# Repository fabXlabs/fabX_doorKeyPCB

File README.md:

# fabX_doorKeyPCB

## Not yet functional

Outdoor Keypad and reader PCB

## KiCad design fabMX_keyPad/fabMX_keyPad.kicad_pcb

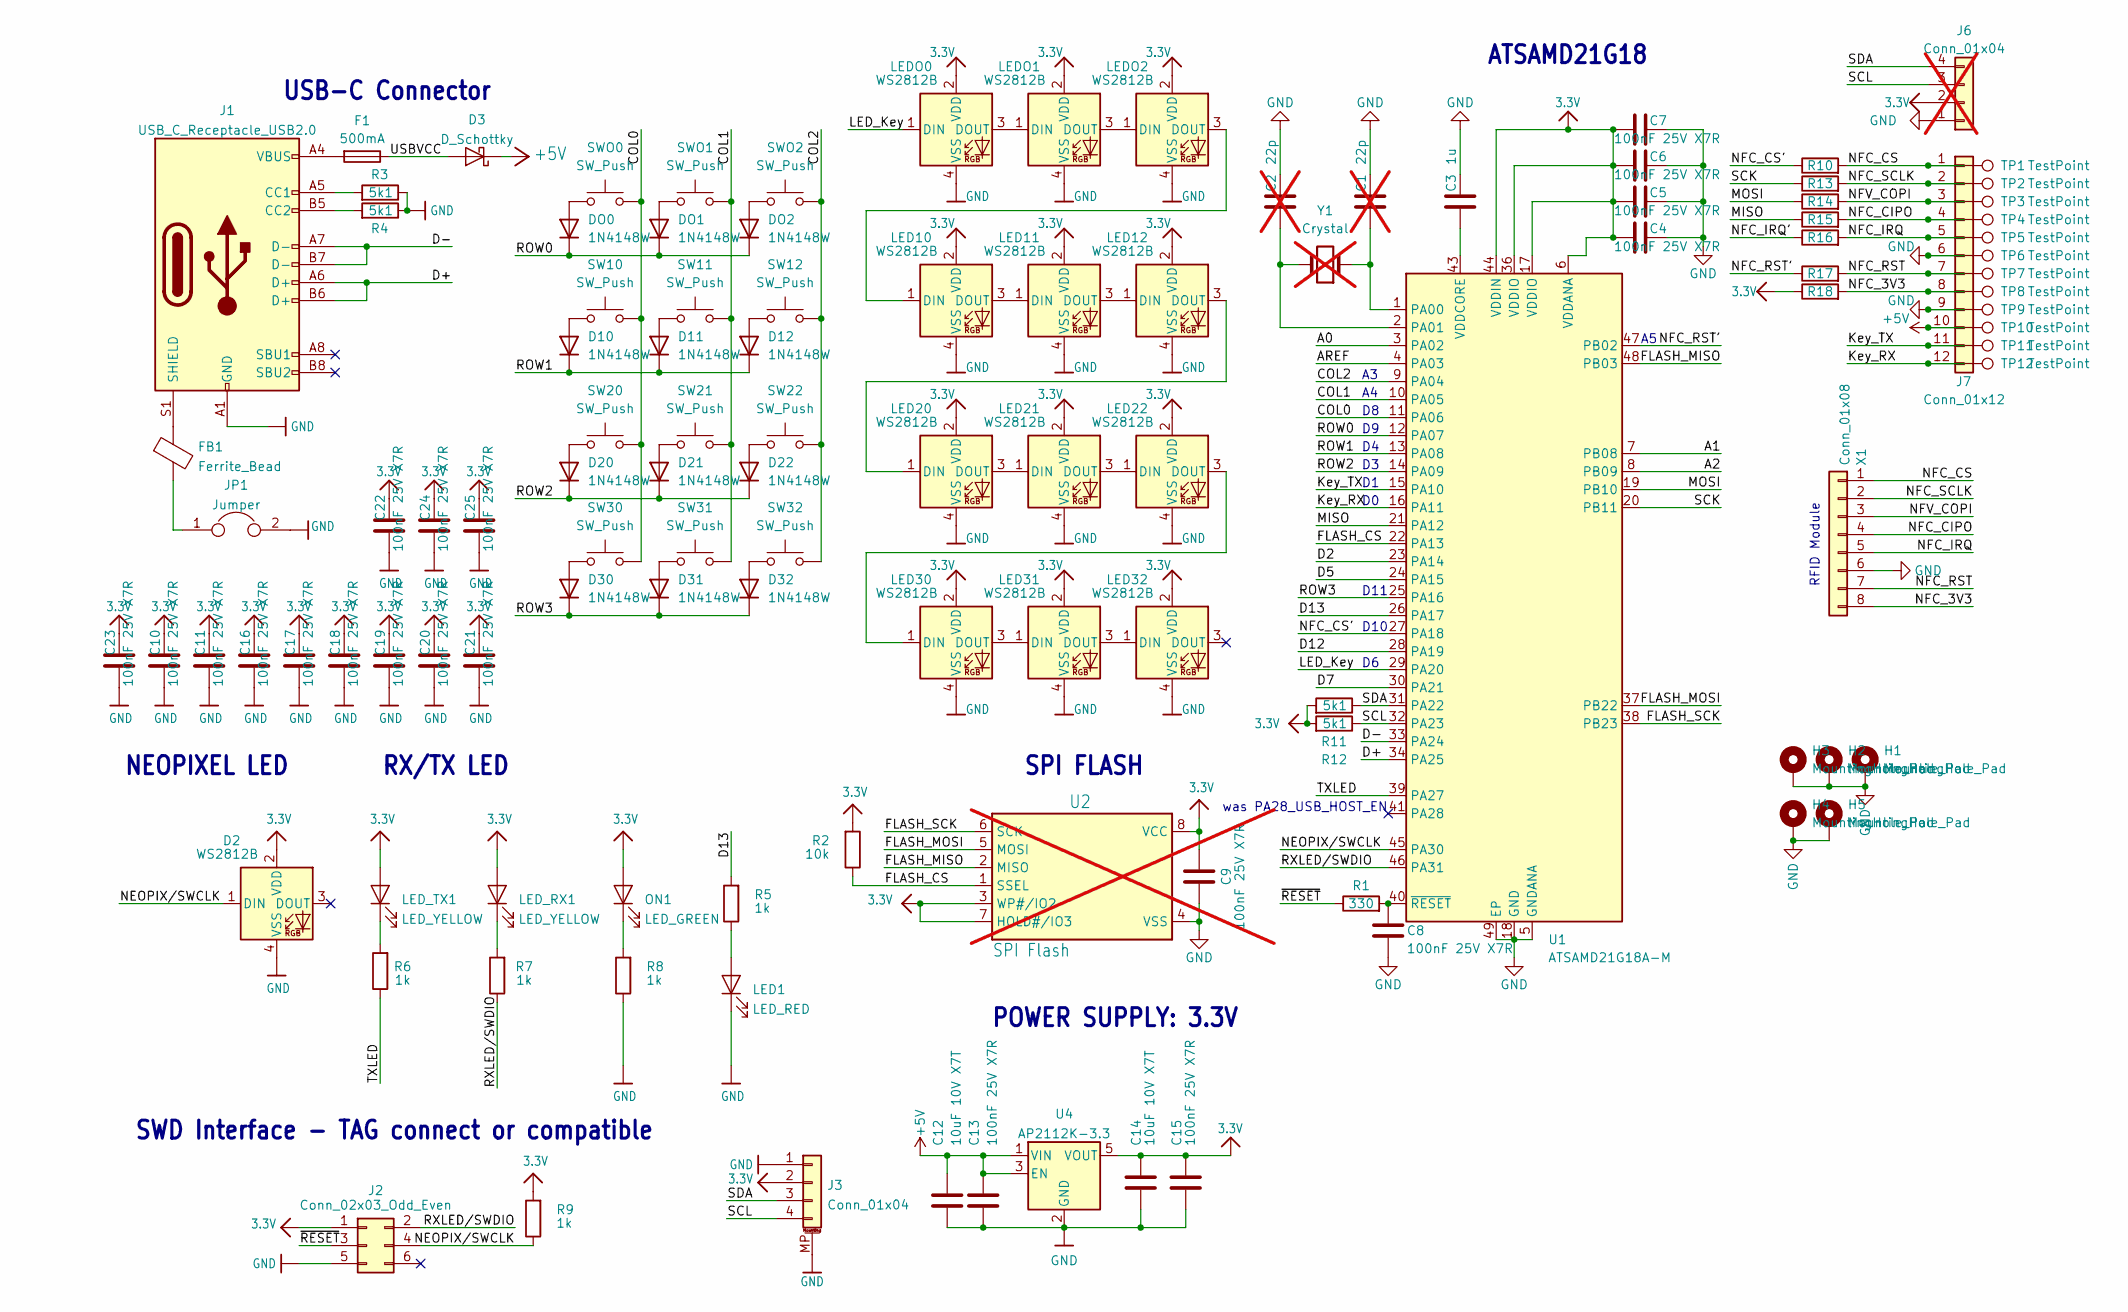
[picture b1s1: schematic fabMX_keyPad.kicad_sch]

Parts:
C1, C2: 22p; C_0603_min; not fitted
C3: 1u; C_0603_min
C4, C5, C6, C7, C8, C9, C10, C11, C13, C15, C16, C17, C18, C19, C20, C21, C22, C23, C24, C25: 100nF 25V X7R; C_0603_min
C12, C14: 10uF 10V X7T; C_0603_min
D2: WS2812B; LED_SK6812_EC15_1.5x1.5mm_modRounded; Digikey# 1528-4492-ND
D3: D_Schottky; D_SOD-123F; Digikey# 4878-SL1MCT-ND
D10, D11, D12, D20, D21, D22, D30, D31, D32: 1N4148W; D_SOD-123; Part# 1N4148W; LCSC# C444720
DO0, DO1, DO2: 1N4148W; D_SOD-123; Part# 1N4148W; LCSC# C444720
F1: 500mA; Fuse_0603_1608Metric; Part# 0402L050SLKR; LCSC# C206938
FB1: Ferrite_Bead; L_0603_min
H1, H2, H3, H4, H5: MountingHole_Pad; MountingHole_2.7mm_M2.5_Pad_Via
J1: USB_C_Receptacle_USB2.0; USB_C_Receptacle_GT-USB-7010; Mouser# 640-USB4105-GF-A; Digikey# 2073-USB4105-GF-ACT-ND
J2: Conn_02x03_Odd_Even; TC2030-NL_SMALL
J3: Conn_01x04; JST_SH_SM04B-SRSS-TB_1x04-1MP_P1.00mm_Horizontal; Part# SM04B-SRSS-TB(LF)(SN); LCSC# C160404
J6: Conn_01x04; PinSocket_1x04_P2.54mm_Vertical_SMD_Pin1Left; Farnell# 3817900; not fitted
J7: Conn_01x12; PhoenixContact_MC_1,5_12-G-3.5_1x12_P3.50mm_Horizontal
JP1: Jumper; SolderJumper-2_P1.3mm_Open_RoundedPad1.0x1.5mm
LED1: LED_RED; LED_0603_min
LED10, LED11, LED12, LED20, LED21, LED22, LED30, LED31, LED32: WS2812B; LED_SK6812_EC15_1.5x1.5mm_modRounded; Digikey# 1528-4492-ND
LEDO0, LEDO1, LEDO2: WS2812B; LED_SK6812_EC15_1.5x1.5mm_modRounded; Digikey# 1528-4492-ND
LED_RX1: LED_YELLOW; LED_0603_min
LED_TX1: LED_YELLOW; LED_0603_min
ON1: LED_GREEN; LED_0603_min
R1: 330; R_0603_min
R2: 10k; R_0603_min
R3, R4, R11, R12: 5k1; R_0603_min
R5, R6, R7, R8, R9: 1k; R_0603_min
R10, R13, R14, R15, R16, R17, R18: 0; R_0603_min
SW10, SW11, SW12, SW20, SW21, SW22, SW30, SW31, SW32: SW_Push; SW_Cherry_MX_PCB
SWO0, SWO1, SWO2: SW_Push; SW_Cherry_MX_PCB
TP1, TP2, TP3, TP4, TP5, TP6, TP7, TP8, TP9, TP10, TP11, TP12: TestPoint; Pad_1.8x5.5mm
U1: ATSAMD21G18A-M; QFN-48-1EP_7x7mm_P0.5mm_EP5.15x5.15mm; Mouser# 556-ATSAMD21G18A-MUT; Digikey# ATSAMD21G18A-MUTCT-ND
U2: SPI Flash; SOIC-8W_5.3x5.3mm_P1.27mm; not fitted
U4: AP2112K-3.3; SOT-23-5; Digikey# AP2112K-3.3TRG1DICT-ND
X1: Conn_01x08; PinSocket_1x08_P2.54mm_Vertical_SMD_Pin1Left
Y1: Crystal; Crystal_SMD_3215-2Pin_3.2x1.5mm; not fitted

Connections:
3.3V: C4.1, C5.1, C6.1, C7.1, C9.1, C10.2, C11.2, C14.1, C15.1, C16.2, C17.2, C18.2, C19.2, C20.2, C21.2, C22.2, C23.2, C24.2, C25.2, D2.2 (VDD), J2.1, J3.2, J6.2, LED10.2 (VDD), LED11.2 (VDD), LED12.2 (VDD), LED20.2 (VDD), LED21.2 (VDD), LED22.2 (VDD), LED30.2 (VDD), LED31.2 (VDD), LED32.2 (VDD), LEDO0.2 (VDD), LEDO1.2 (VDD), LEDO2.2 (VDD), LED_RX1.2 (A), LED_TX1.2 (A), ON1.2 (A), R2.2, R9.2, R11.2, R12.2, R18.1, U1.6 (VDDANA), U1.17 (VDDIO), U1.36 (VDDIO), U1.44 (VDDIN), U2.3 (WP#/IO2), U2.7 (HOLD#/IO3), U2.8 (VCC), U4.5 (VOUT)
+5V: C12.1, C13.1, D3.1 (K), J7.10, TP10.1, U4.1 (VIN), U4.3 (EN)
/A0: U1.3 (PA02)
/A1: U1.7 (PB08)
/A2: U1.8 (PB09)
/AREF: U1.4 (PA03)
/COL0: SW10.2, SW20.2, SW30.2, SWO0.2, U1.11 (PA06)
/COL1: SW11.2, SW21.2, SW31.2, SWO1.2, U1.10 (PA05)
/COL2: SW12.2, SW22.2, SW32.2, SWO2.2, U1.9 (PA04)
/D2: U1.23 (PA14)
/D5: U1.24 (PA15)
/D7: U1.30 (PA21)
/D12: U1.28 (PA19)
/D13: R5.2, U1.26 (PA17)
/D+: J1.A6 (D+), J1.B6 (D+), U1.34 (PA25)
/D-: J1.A7 (D-), J1.B7 (D-), U1.33 (PA24)
/FLASH_CS: R2.1, U1.22 (PA13), U2.1 (SSEL)
/FLASH_MISO: U1.48 (PB03), U2.2 (MISO)
/FLASH_MOSI: U1.37 (PB22), U2.5 (MOSI)
/FLASH_SCK: U1.38 (PB23), U2.6 (SCK)
/Key_RX: J7.12, TP12.1, U1.16 (PA11)
/Key_TX: J7.11, TP11.1, U1.15 (PA10)
/LED_Key: LEDO0.1 (DIN), U1.29 (PA20)
/MISO: R15.1, U1.21 (PA12)
/MOSI: R14.1, U1.19 (PB10)
/NEOPIX/SWCLK: D2.1 (DIN), J2.4, R9.1, U1.45 (PA30)
/NFC_3V3: J7.8, R18.2, TP8.1, X1.8
/NFC_CIPO: J7.4, R15.2, TP4.1, X1.4
/NFC_CS: J7.1, R10.2, TP1.1, X1.1
/NFC_CS': R10.1, U1.27 (PA18)
/NFC_IRQ: J7.5, R16.2, TP5.1, X1.5
/NFC_IRQ': R16.1
/NFC_RST: J7.7, R17.2, TP7.1, X1.7
/NFC_RST': R17.1, U1.47 (PB02)
/NFC_SCLK: J7.2, R13.2, TP2.1, X1.2
/NFV_COPI: J7.3, R14.2, TP3.1, X1.3
/ROW0: DO0.1 (K), DO1.1 (K), DO2.1 (K), U1.12 (PA07)
/ROW1: D10.1 (K), D11.1 (K), D12.1 (K), U1.13 (PA08)
/ROW2: D20.1 (K), D21.1 (K), D22.1 (K), U1.14 (PA09)
/ROW3: D30.1 (K), D31.1 (K), D32.1 (K), U1.25 (PA16)
/RXLED/SWDIO: J2.2, R7.1, U1.46 (PA31)
/SCK: R13.1, U1.20 (PB11)
/SCL: J3.4, J6.3, R12.1, U1.32 (PA23)
/SDA: J3.3, J6.4, R11.1, U1.31 (PA22)
/TXLED: R6.1, U1.39 (PA27)
/USBVCC: D3.2 (A), F1.1
/~RESET: J2.3, R1.1
GND: C1.1, C2.1, C3.1, C4.2, C5.2, C6.2, C7.2, C8.2, C9.2, C10.1, C11.1, C12.2, C13.2, C14.2, C15.2, C16.1, C17.1, C18.1, C19.1, C20.1, C21.1, C22.1, C23.1, C24.1, C25.1, D2.4 (VSS), H1.1, H2.1, H3.1, H4.1, H5.1, J1.A1 (GND), J1.A12 (GND), J1.B1 (GND), J1.B12 (GND), J2.5, J3.1, J3.MP (MountPin), J6.1, J7.6, J7.9, JP1.2, LED1.1 (K), LED10.4 (VSS), LED11.4 (VSS), LED12.4 (VSS), LED20.4 (VSS), LED21.4 (VSS), LED22.4 (VSS), LED30.4 (VSS), LED31.4 (VSS), LED32.4 (VSS), LEDO0.4 (VSS), LEDO1.4 (VSS), LEDO2.4 (VSS), R3.1, R4.1, R8.1, TP6.1, TP9.1, U1.5 (GNDANA), U1.18 (GND), U1.35 (GND), U1.42 (GND), U1.49 (EP), U2.4 (VSS), U4.2 (GND), X1.6
unnamed: D10.2 (A), SW10.1
unnamed: D11.2 (A), SW11.1
unnamed: D12.2 (A), SW12.1
unnamed: D20.2 (A), SW20.1
unnamed: D21.2 (A), SW21.1
unnamed: D22.2 (A), SW22.1
unnamed: D30.2 (A), SW30.1
unnamed: D31.2 (A), SW31.1
unnamed: D32.2 (A), SW32.1
unnamed: DO0.2 (A), SWO0.1
unnamed: DO1.2 (A), SWO1.1
unnamed: DO2.2 (A), SWO2.1
unnamed: F1.2, J1.A4 (VBUS), J1.A9 (VBUS), J1.B4 (VBUS), J1.B9 (VBUS)
unnamed: FB1.2, JP1.1
unnamed: J1.A5 (CC1), R3.2
unnamed: J1.B5 (CC2), R4.2
unnamed: FB1.1, J1.S1 (SHIELD)
unnamed: LED1.2 (A), R5.1
unnamed: LED10.1 (DIN), LEDO2.3 (DOUT)
unnamed: LED10.3 (DOUT), LED11.1 (DIN)
unnamed: LED11.3 (DOUT), LED12.1 (DIN)
unnamed: LED12.3 (DOUT), LED20.1 (DIN)
unnamed: LED20.3 (DOUT), LED21.1 (DIN)
unnamed: LED21.3 (DOUT), LED22.1 (DIN)
unnamed: LED22.3 (DOUT), LED30.1 (DIN)
unnamed: LED30.3 (DOUT), LED31.1 (DIN)
unnamed: LED31.3 (DOUT), LED32.1 (DIN)
unnamed: LEDO0.3 (DOUT), LEDO1.1 (DIN)
unnamed: LEDO1.3 (DOUT), LEDO2.1 (DIN)
unnamed: LED_RX1.1 (K), R7.2
unnamed: LED_TX1.1 (K), R6.2
unnamed: ON1.1 (K), R8.2
unnamed: C1.2, U1.1 (PA00), Y1.1
unnamed: C2.2, U1.2 (PA01), Y1.2
unnamed: C3.2, U1.43 (VDDCORE)
unnamed: C8.1, R1.2, U1.40 (~RESET)

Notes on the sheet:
RX/TX LED
USB-C Connector
SWD Interface - TAG connect or compatible
was PA28_USB_HOST_EN
POWER SUPPLY: 3.3V
SPI FLASH
ATSAMD21G18
RFID Module
D10
NEOPIXEL LED
D11

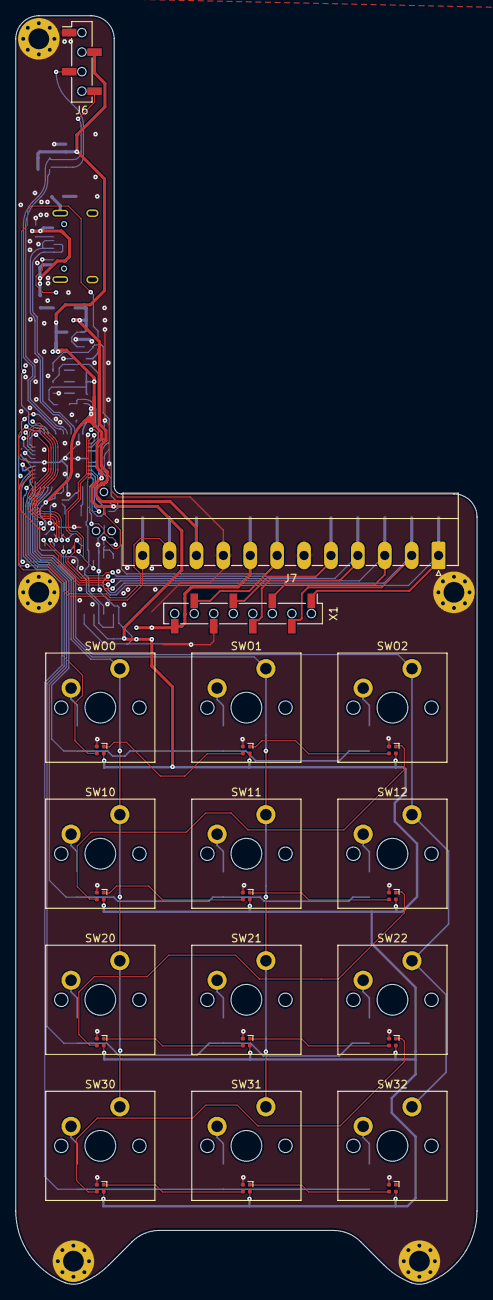
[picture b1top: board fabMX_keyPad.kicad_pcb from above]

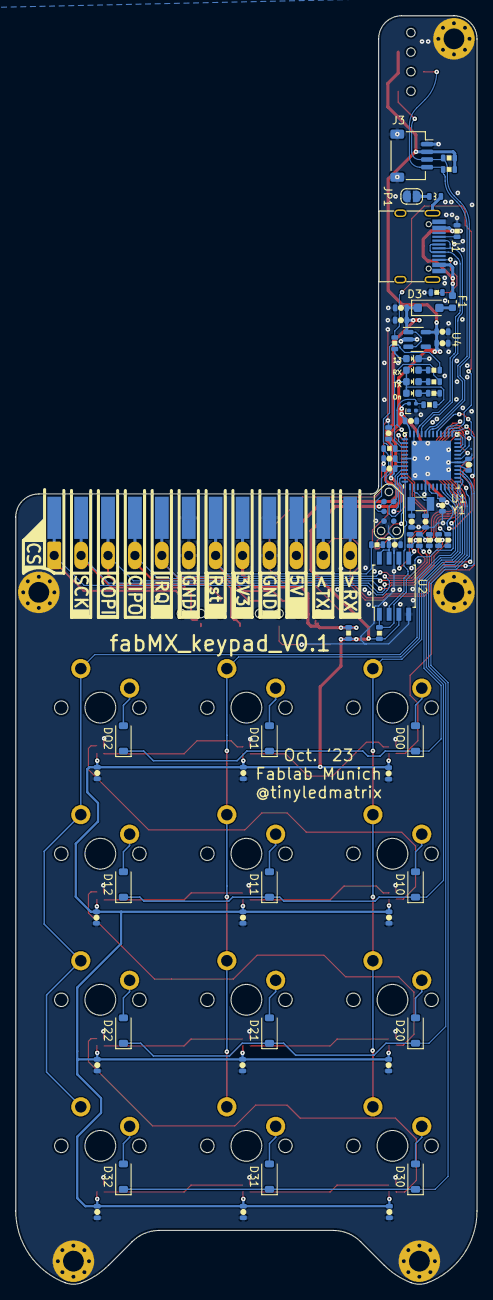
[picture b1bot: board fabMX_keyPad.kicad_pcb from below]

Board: 2 copper layers, 60.0 x 165.0 mm, 115 parts (83 on the bottom side), 75 nets.

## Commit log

2023-03-06 Create LICENSE
2023-12-28 Added PCB files
2024-01-02 Fixes from @fkreiner 's feedback at 37C3
    Connected NFC_CS' and NFC_RST' signals to MCU
    Added additional Jumper-R to connect NFC_3V3 to global 3.3V net
2024-01-02 DRC and minor fix
    DRC okay
2024-02-22 some Work on BOM
    work not yet finished...wait for more updates before odering please
2024-02-29 BOM update + move to kicad8
2024-02-29 Files for case
